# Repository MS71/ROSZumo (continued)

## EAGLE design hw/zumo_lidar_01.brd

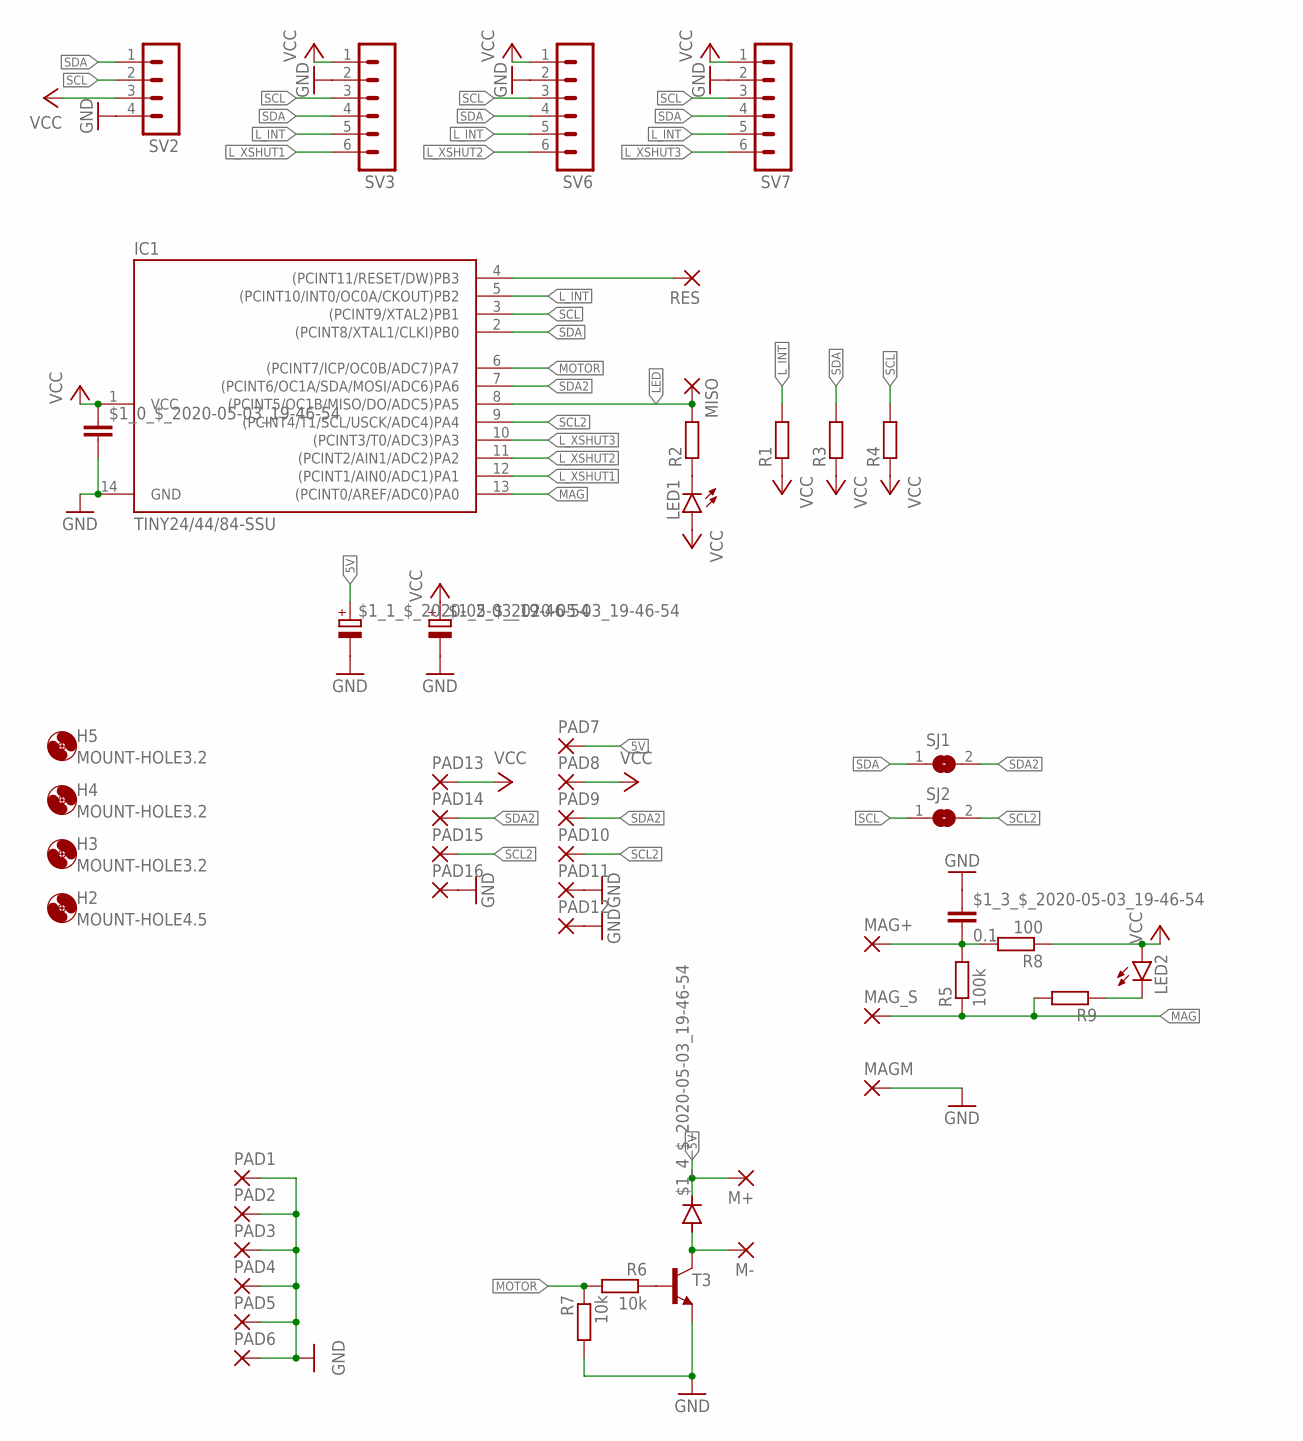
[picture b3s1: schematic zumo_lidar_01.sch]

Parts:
$1_0_$_2020-05-03_19-46-54: C-EUC0805; C0805
$1_1_$_2020-05-03_19-46-54, $1_2_$_2020-05-03_19-46-54: CPOL-EUSMCC; SMC_C
$1_3_$_2020-05-03_19-46-54: 0.1; C0805
$1_4_$_2020-05-03_19-46-54: DIODE-MINIMELF; MINIMELF
H2: MOUNT-HOLE4.5; 4,5
H3, H4, H5: MOUNT-HOLE3.2; 3,2
IC1: TINY24/44/84-SSU; SOIC14
LED1, LED2: LEDSML0805; SML0805
M+: 1,6/0,8
M-: 1,6/0,8
MAG+: 1,6/0,8
MAGM: 1,6/0,8
MAG_S: 1,6/0,8
MISO: 1,6/0,8
PAD1, PAD2, PAD3, PAD4, PAD5, PAD6: 2,54/1,1
PAD7, PAD8, PAD9, PAD10, PAD11, PAD12, PAD13, PAD14, PAD15, PAD16: 1,6/0,8
R1, R2, R3, R4, R9: R-EU_M0805; M0805
R5: 100k; M0805
R6, R7: 10k; R0805
R8: 100; M0805
RES: 1,6/0,8
SJ1, SJ2: SJ
SV2: MA04-1
SV3, SV6, SV7: MA06-1
T3: BC817-16-NPN-SOT23-BEC; SOT23-BEC

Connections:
5V: $1_1_$_2020-05-03_19-46-54.+, $1_4_$_2020-05-03_19-46-54.C, M+.1, PAD7.1
GND: $1_0_$_2020-05-03_19-46-54.2, $1_1_$_2020-05-03_19-46-54.-, $1_2_$_2020-05-03_19-46-54.-, $1_3_$_2020-05-03_19-46-54.1, IC1.14 (GND), MAGM.1, PAD1.1, PAD2.1, PAD3.1, PAD4.1, PAD5.1, PAD6.1, PAD11.1, PAD12.1, PAD16.1, R7.2, SV2.4, SV3.2, SV6.2, SV7.2, T3.E
LED: IC1.8 ((PCINT5/OC1B/MISO/DO/ADC5)PA5), MISO.1, R2.2
L_INT: IC1.5 ((PCINT10/INT0/OC0A/CKOUT)PB2), R1.2, SV3.5, SV6.5, SV7.5
L_XSHUT1: IC1.12 ((PCINT1/AIN0/ADC1)PA1), SV3.6
L_XSHUT2: IC1.11 ((PCINT2/AIN1/ADC2)PA2), SV6.6
L_XSHUT3: IC1.10 ((PCINT3/T0/ADC3)PA3), SV7.6
MAG: IC1.13 ((PCINT0/AREF/ADC0)PA0), MAG_S.1, R5.1, R9.2
MAGVCC: $1_3_$_2020-05-03_19-46-54.2, MAG+.1, R5.2, R8.2
MOTOR: IC1.6 ((PCINT7/ICP/OC0B/ADC7)PA7), R6.2, R7.1
unnamed: LED1.C, R2.1
unnamed: $1_4_$_2020-05-03_19-46-54.A, M-.1, T3.C
unnamed: R6.1, T3.B
unnamed: LED2.C, R9.1
RESET: IC1.4 ((PCINT11/RESET/DW)PB3), RES.1
SCL: IC1.3 ((PCINT9/XTAL2)PB1), R4.2, SJ2.1, SV2.2, SV3.3, SV6.3, SV7.3
SCL2: IC1.9 ((PCINT4/T1/SCL/USCK/ADC4)PA4), PAD10.1, PAD15.1, SJ2.2
SDA: IC1.2 ((PCINT8/XTAL1/CLKI)PB0), R3.2, SJ1.1, SV2.1, SV3.4, SV6.4, SV7.4
SDA2: IC1.7 ((PCINT6/OC1A/SDA/MOSI/ADC6)PA6), PAD9.1, PAD14.1, SJ1.2
VCC: $1_0_$_2020-05-03_19-46-54.1, $1_2_$_2020-05-03_19-46-54.+, IC1.1 (VCC), LED1.A, LED2.A, PAD8.1, PAD13.1, R1.1, R3.1, R4.1, R8.1, SV2.3, SV3.1, SV6.1, SV7.1

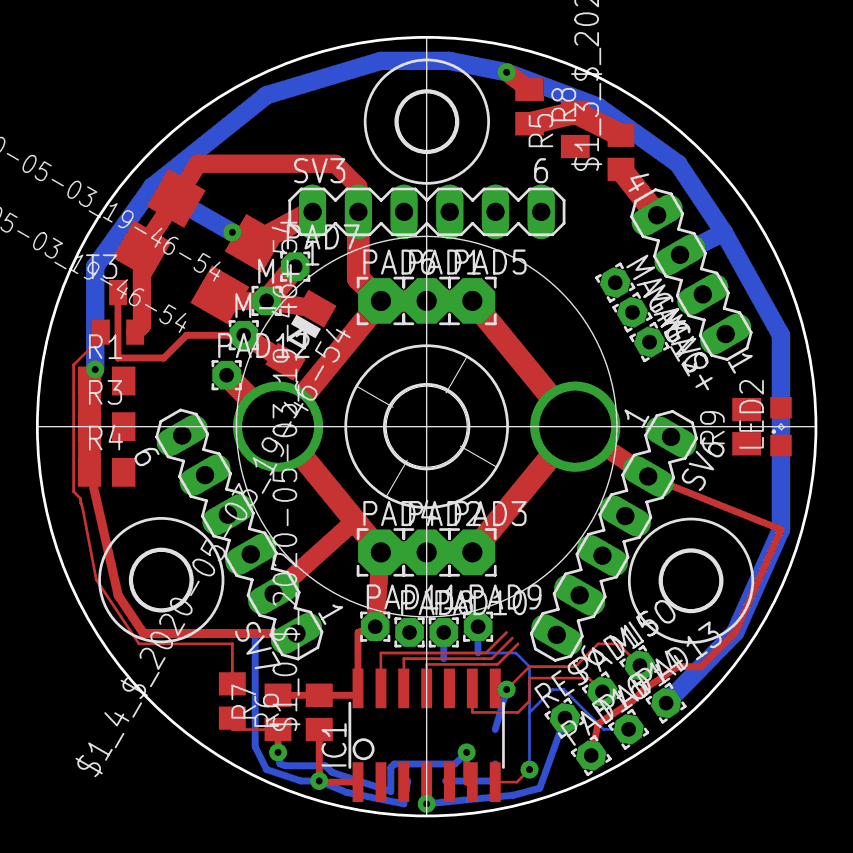
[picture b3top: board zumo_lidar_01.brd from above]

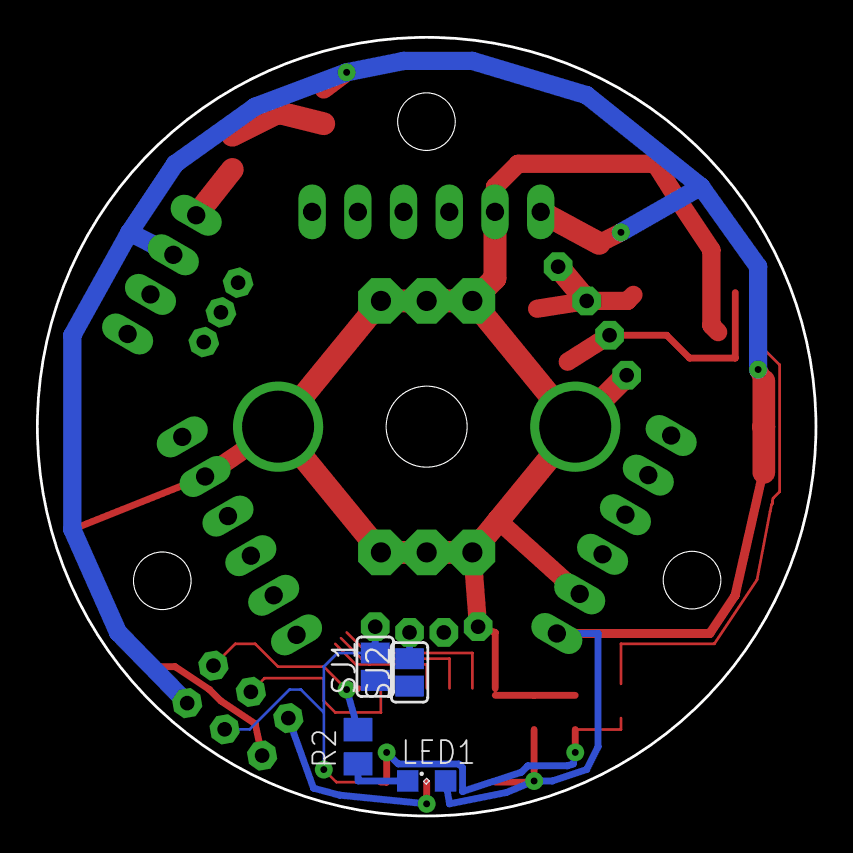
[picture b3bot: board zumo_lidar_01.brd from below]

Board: 2 copper layers, 43.3 x 43.3 mm, 51 parts (4 on the bottom side), 20 nets.

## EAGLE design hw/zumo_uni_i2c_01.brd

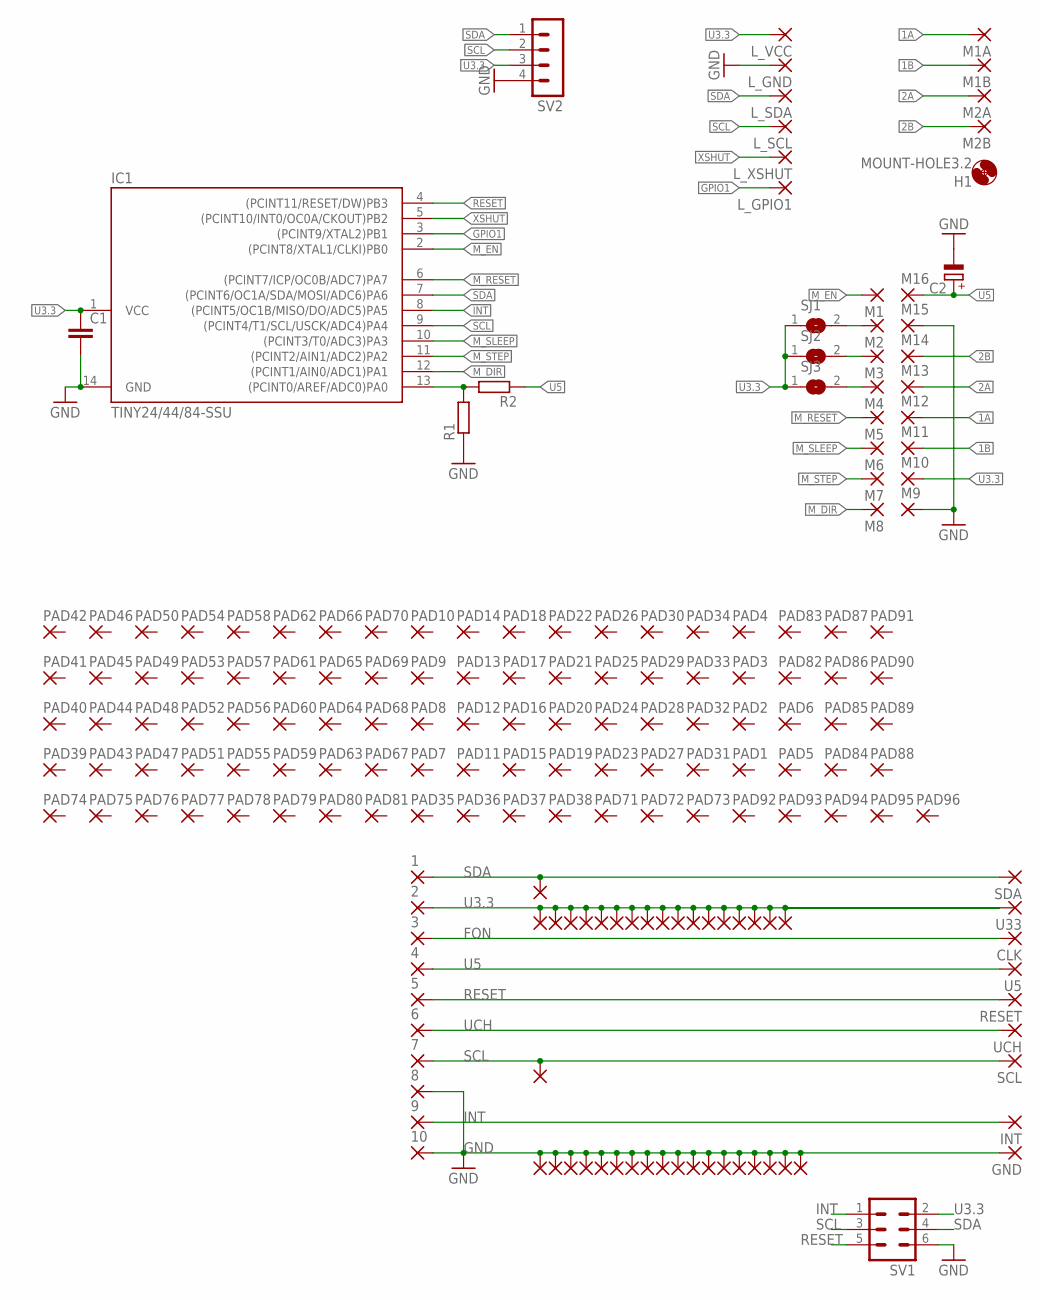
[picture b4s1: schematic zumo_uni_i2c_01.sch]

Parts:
1, 2, 3, 4, 5, 6, 7, 8, 9, 10: SMD2; SMD1,27-2,54
C1: C-EUC0805; C0805
C2: CPOL-EUSMCC; SMC_C
CLK: 1,6/0,9
GND: 1,6/0,9
H1: MOUNT-HOLE3.2; 3,2
IC1: TINY24/44/84-SSU; SOIC14
INT: 1,6/0,9
L_GND: 1,6/0,8
L_GPIO1: 1,6/0,8
L_SCL: 1,6/0,8
L_SDA: 1,6/0,8
L_VCC: 1,6/0,8
L_XSHUT: 1,6/0,8
M1, M2, M3, M4, M5, M6, M7, M8, M9, M10, M11, M12, M13, M14, M15, M16: 1,6/0,9
M1A, M1B, M2A, M2B: 1,6/0,8
MISO1, MISO4, MISO5, MISO6, MISO7, MISO8, MISO9, MISO10, MISO11, MISO12, MISO13, MISO14, MISO15, MISO16, MISO17, MISO18, MISO19, MISO20, MISO21, MISO22, MISO23, MISO24, MISO25, MISO26, MISO27, MISO28, MISO29, MISO30, MISO31, MISO32, MISO33, MISO34, MISO35, MISO36, MISO37, MISO41, MISO43: 1,6/0,9
PAD1, PAD2, PAD3, PAD4, PAD5, PAD6, PAD7, PAD8, PAD9, PAD10, PAD11, PAD12, PAD13, PAD14, PAD15, PAD16, PAD17, PAD18, PAD19, PAD20, PAD21, PAD22, PAD23, PAD24, PAD25, PAD26, PAD27, PAD28, PAD29, PAD30, PAD31, PAD32, PAD33, PAD34, PAD35, PAD36, PAD37, PAD38, PAD39, PAD40, PAD41, PAD42, PAD43, PAD44, PAD45, PAD46, PAD47, PAD48, PAD49, PAD50, PAD51, PAD52, PAD53, PAD54, PAD55, PAD56, PAD57, PAD58, PAD59, PAD60, PAD61, PAD62, PAD63, PAD64, PAD65, PAD66, PAD67, PAD68, PAD69, PAD70, PAD71, PAD72, PAD73, PAD74, PAD75, PAD76, PAD77, PAD78, PAD79, PAD80, PAD81, PAD82, PAD83, PAD84, PAD85, PAD86, PAD87, PAD88, PAD89, PAD90, PAD91, PAD92, PAD93, PAD94, PAD95, PAD96: 1,6/0,9
R1, R2: R-EU_M0805; M0805
RESET: 1,6/0,9
SCL: 1,6/0,9
SDA: 1,6/0,9
SJ1, SJ2, SJ3: SJ
SV1: ML6
SV2: MA04-1
U5, U33: 1,6/0,9
UCH: 1,6/0,9

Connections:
1A: M1A.1, M12.1
1B: M1B.1, M11.1
2A: M2A.1, M13.1
2B: M2B.1, M14.1
FON: 3.1, CLK.1
GND: 8.1, 10.1, C1.2, C2.-, GND.1, IC1.14 (GND), L_GND.1, M9.1, M15.1, MISO1.1, MISO5.1, MISO6.1, MISO7.1, MISO8.1, MISO9.1, MISO10.1, MISO11.1, MISO12.1, MISO13.1, MISO14.1, MISO15.1, MISO16.1, MISO17.1, MISO18.1, MISO19.1, MISO20.1, MISO43.1, R1.1, SV1.6, SV2.4
GPIO1: IC1.3 ((PCINT9/XTAL2)PB1), L_GPIO1.1
INT: 9.1, IC1.8 ((PCINT5/OC1B/MISO/DO/ADC5)PA5), INT.1, SV1.1
M_DIR: IC1.12 ((PCINT1/AIN0/ADC1)PA1), M8.1
M_EN: IC1.2 ((PCINT8/XTAL1/CLKI)PB0), M1.1
M_MS1: M2.1, SJ1.2
M_MS2: M3.1, SJ2.2
M_MS3: M4.1, SJ3.2
M_RESET: IC1.6 ((PCINT7/ICP/OC0B/ADC7)PA7), M5.1
M_SLEEP: IC1.10 ((PCINT3/T0/ADC3)PA3), M6.1
M_STEP: IC1.11 ((PCINT2/AIN1/ADC2)PA2), M7.1
unnamed: IC1.13 ((PCINT0/AREF/ADC0)PA0), R1.2, R2.2
RESET: 5.1, IC1.4 ((PCINT11/RESET/DW)PB3), RESET.1, SV1.5
SCL: 7.1, IC1.9 ((PCINT4/T1/SCL/USCK/ADC4)PA4), L_SCL.1, MISO41.1, SCL.1, SV1.3, SV2.2
SDA: 1.1, IC1.7 ((PCINT6/OC1A/SDA/MOSI/ADC6)PA6), L_SDA.1, MISO21.1, SDA.1, SV1.4, SV2.1
U3.3: 2.1, C1.1, IC1.1 (VCC), L_VCC.1, M10.1, MISO4.1, MISO22.1, MISO23.1, MISO24.1, MISO25.1, MISO26.1, MISO27.1, MISO28.1, MISO29.1, MISO30.1, MISO31.1, MISO32.1, MISO33.1, MISO34.1, MISO35.1, MISO36.1, MISO37.1, SJ1.1, SJ2.1, SJ3.1, SV1.2, SV2.3, U33.1
U5: 4.1, C2.+, M16.1, R2.1, U5.1
UCH: 6.1, UCH.1
XSHUT: IC1.5 ((PCINT10/INT0/OC0A/CKOUT)PB2), L_XSHUT.1

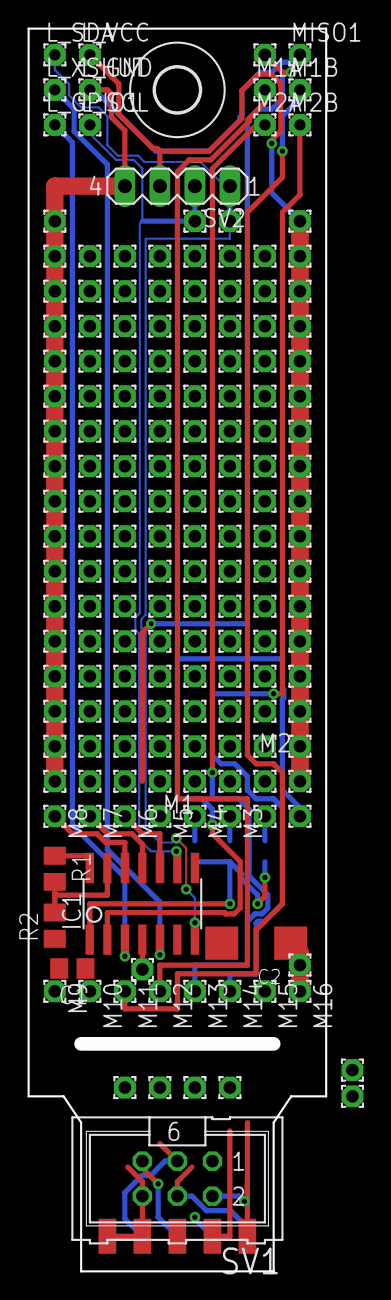
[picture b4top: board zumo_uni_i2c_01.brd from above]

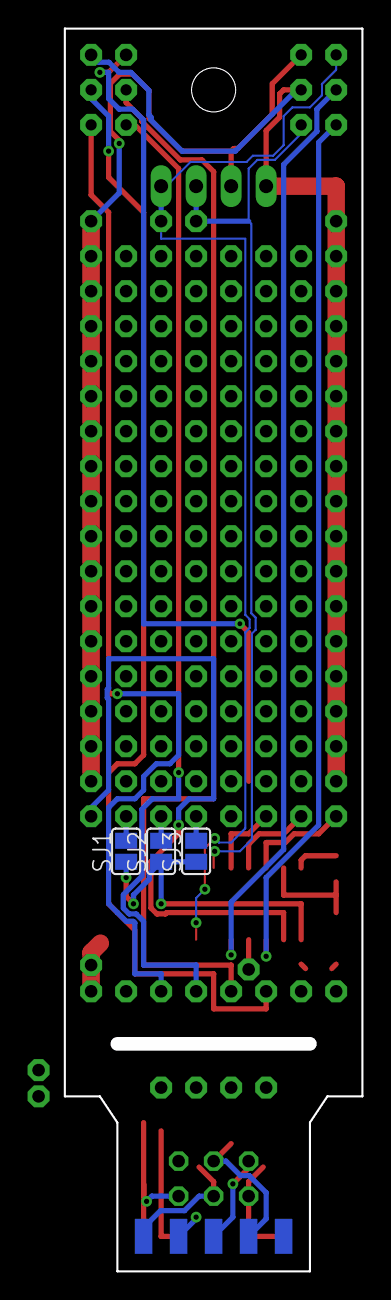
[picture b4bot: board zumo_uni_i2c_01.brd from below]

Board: 2 copper layers, 21.6 x 90.2 mm, 189 parts (8 on the bottom side), 24 nets.

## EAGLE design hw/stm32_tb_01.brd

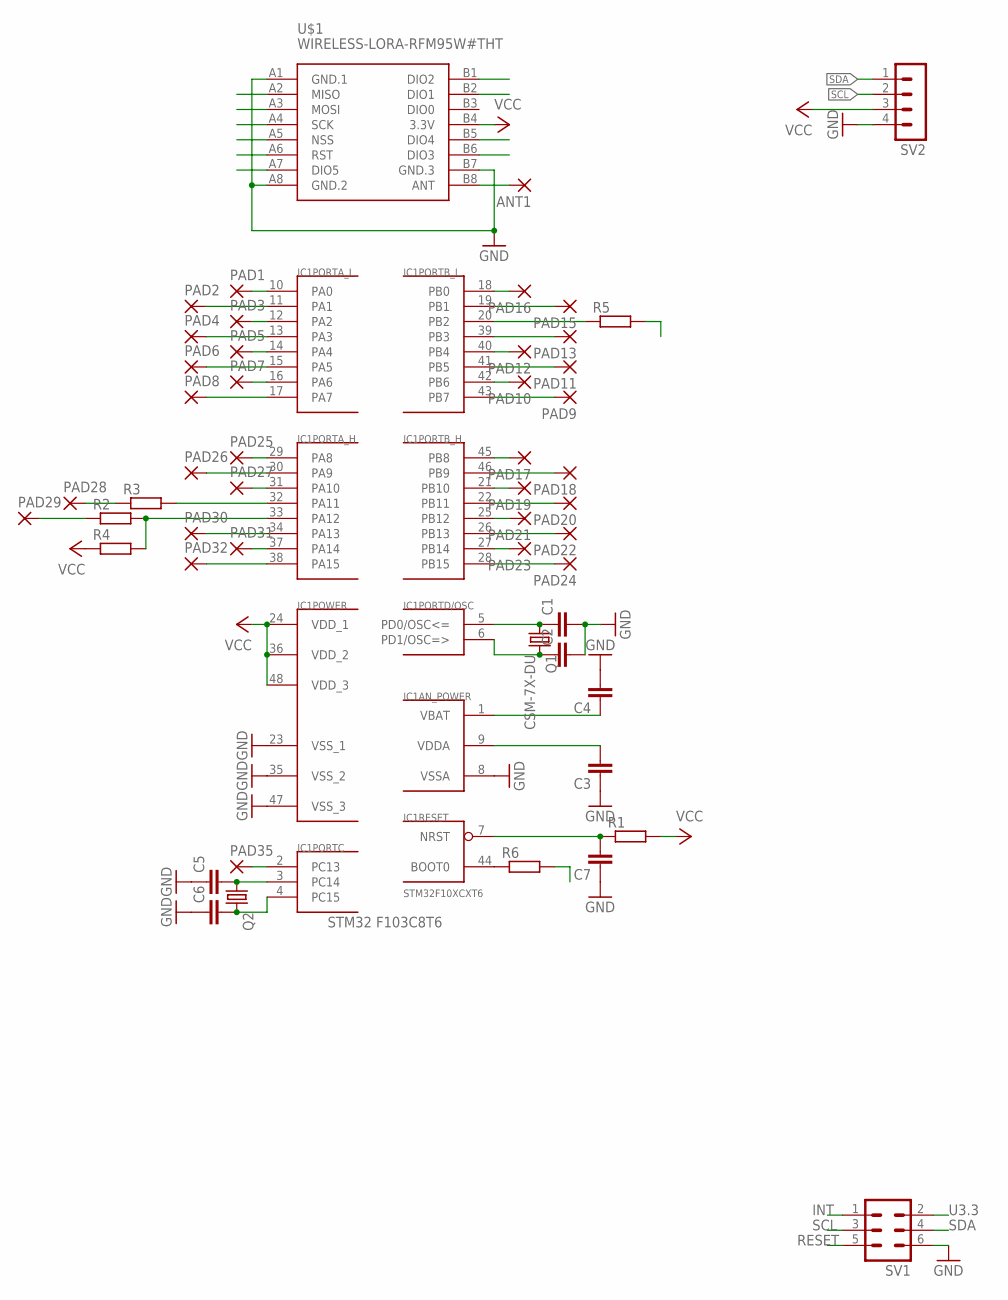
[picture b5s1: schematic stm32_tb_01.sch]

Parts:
ANT1: 1,6/0,9
C1, C2, C3, C4, C5, C6, C7: C-EUC0805; C0805
IC1: STM32F10XCXT6; TQFP48
PAD1, PAD2, PAD3, PAD4, PAD5, PAD6, PAD7, PAD8, PAD9, PAD10, PAD11, PAD12, PAD13, PAD15, PAD16, PAD17, PAD18, PAD19, PAD20, PAD21, PAD22, PAD23, PAD24, PAD25, PAD26, PAD27, PAD28, PAD29, PAD30, PAD31, PAD32, PAD35: 1,6/0,9
Q1: CSM-7X-DU
Q2: CRYSTALTC26V; TC26V
R1, R2, R3, R4, R5, R6: R-EU_R0805; R0805
SV1: ML6
SV2: MA04-1
U$1: WIRELESS-LORA-RFM95W#THT

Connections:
GND: C1.2, C2.2, C3.1, C4.2, C5.1, C6.1, C7.1, IC1.8 (VSSA), IC1.23 (VSS_1), IC1.35 (VSS_2), IC1.47 (VSS_3), SV1.6, SV2.4, U$1.A1 (GND.1), U$1.A8 (GND.2), U$1.B7 (GND.3)
INT: SV1.1
unnamed: IC1.10 (PA0), PAD1.1
unnamed: IC1.11 (PA1), PAD2.1
unnamed: IC1.12 (PA2), PAD3.1
unnamed: IC1.13 (PA3), PAD4.1
unnamed: IC1.14 (PA4), PAD5.1
unnamed: IC1.15 (PA5), PAD6.1
unnamed: IC1.16 (PA6), PAD7.1
unnamed: IC1.17 (PA7), PAD8.1
unnamed: IC1.43 (PB7), PAD9.1
unnamed: IC1.42 (PB6), PAD10.1
unnamed: IC1.41 (PB5), PAD11.1
unnamed: IC1.40 (PB4), PAD12.1
unnamed: IC1.39 (PB3), PAD13.1
unnamed: IC1.20 (PB2), R5.1
unnamed: IC1.19 (PB1), PAD15.1
unnamed: IC1.18 (PB0), PAD16.1
unnamed: IC1.45 (PB8), PAD17.1
unnamed: IC1.46 (PB9), PAD18.1
unnamed: IC1.21 (PB10), PAD19.1
unnamed: IC1.22 (PB11), PAD20.1
unnamed: IC1.25 (PB12), PAD21.1
unnamed: IC1.26 (PB13), PAD22.1
unnamed: IC1.27 (PB14), PAD23.1
unnamed: IC1.28 (PB15), PAD24.1
unnamed: IC1.29 (PA8), PAD25.1
unnamed: IC1.30 (PA9), PAD26.1
unnamed: IC1.31 (PA10), PAD27.1
unnamed: IC1.33 (PA12), R2.2, R4.2
unnamed: IC1.32 (PA11), R3.2
unnamed: IC1.34 (PA13), PAD30.1
unnamed: IC1.37 (PA14), PAD31.1
unnamed: IC1.38 (PA15), PAD32.1
unnamed: PAD28.1, R3.1
unnamed: PAD29.1, R2.1
unnamed: IC1.2 (PC13), PAD35.1
unnamed: C5.2, IC1.3 (PC14), Q2.1
unnamed: C6.2, IC1.4 (PC15), Q2.2
unnamed: IC1.44 (BOOT0), R6.1
unnamed: C1.1, IC1.5 (PD0/OSC<=), Q1.1
unnamed: C2.1, IC1.6 (PD1/OSC=>), Q1.2
unnamed: C3.2, IC1.9 (VDDA)
unnamed: C4.1, IC1.1 (VBAT)
unnamed: C7.2, IC1.7 (NRST), R1.1
unnamed: ANT1.1, U$1.B8 (ANT)
RESET: SV1.5
SCL: SV1.3, SV2.2
SDA: SV1.4, SV2.1
U3.3: SV1.2
VCC: IC1.24 (VDD_1), IC1.36 (VDD_2), IC1.48 (VDD_3), R1.2, R4.1, SV2.3, U$1.B4 (3.3V)

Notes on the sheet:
STM32 F103C8T6

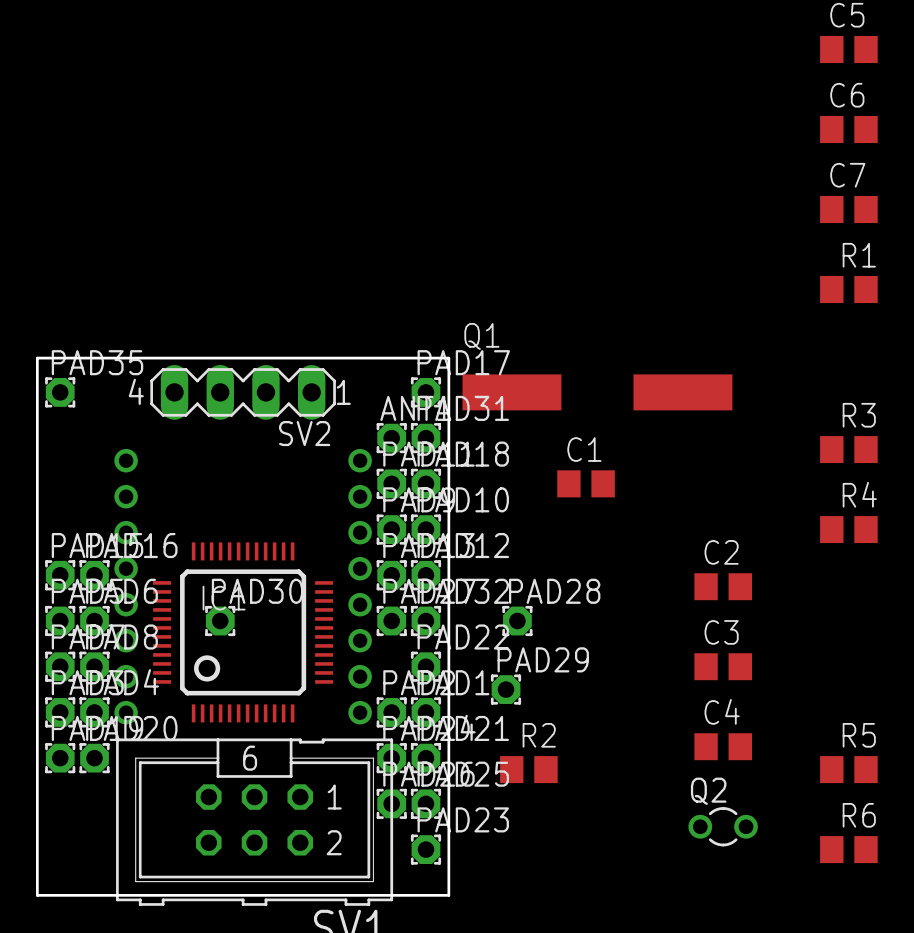
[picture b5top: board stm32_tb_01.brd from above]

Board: 2 copper layers, 22.9 x 29.8 mm, 52 parts (1 on the bottom side), 48 nets.

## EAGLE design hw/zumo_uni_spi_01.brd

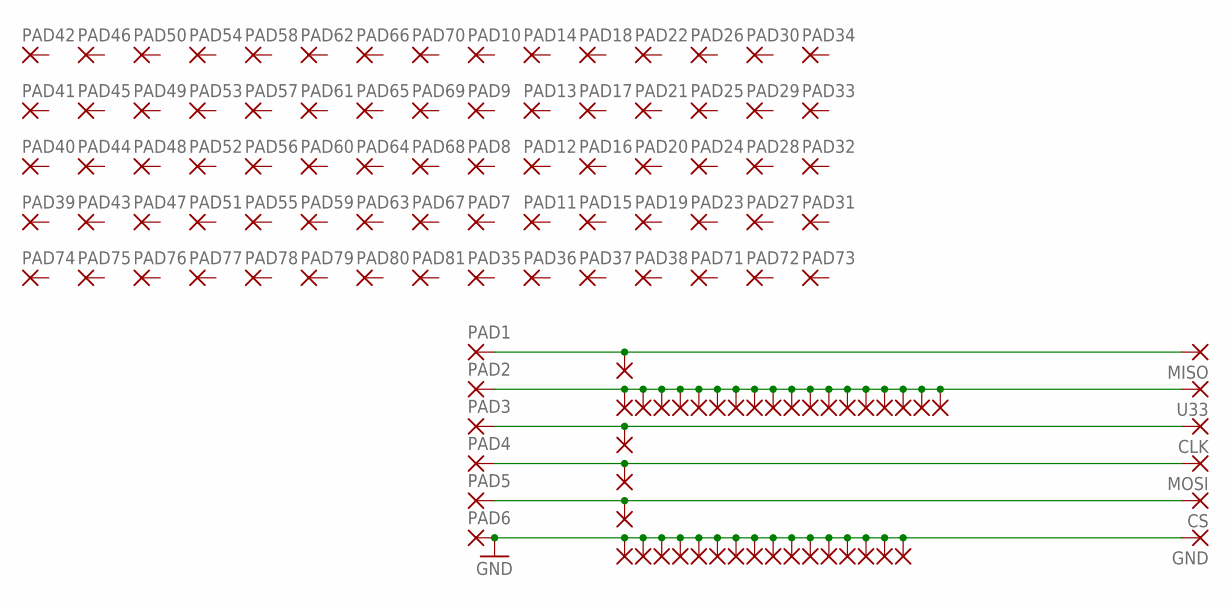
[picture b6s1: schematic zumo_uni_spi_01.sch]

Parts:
CLK: 1,6/0,9
CS: 1,6/0,9
GND: 1,6/0,9
MISO, MISO1, MISO2, MISO3, MISO4, MISO5, MISO6, MISO7, MISO8, MISO9, MISO10, MISO11, MISO12, MISO13, MISO14, MISO15, MISO16, MISO17, MISO18, MISO19, MISO20, MISO21, MISO22, MISO23, MISO24, MISO25, MISO26, MISO27, MISO28, MISO29, MISO30, MISO31, MISO32, MISO33, MISO34, MISO35, MISO36, MISO37, MISO38: 1,6/0,9
MOSI: 1,6/0,9
PAD1, PAD2, PAD3, PAD4, PAD5, PAD6: SMD2; SMD1,27-2,54
PAD7, PAD8, PAD9, PAD10, PAD11, PAD12, PAD13, PAD14, PAD15, PAD16, PAD17, PAD18, PAD19, PAD20, PAD21, PAD22, PAD23, PAD24, PAD25, PAD26, PAD27, PAD28, PAD29, PAD30, PAD31, PAD32, PAD33, PAD34, PAD35, PAD36, PAD37, PAD38, PAD39, PAD40, PAD41, PAD42, PAD43, PAD44, PAD45, PAD46, PAD47, PAD48, PAD49, PAD50, PAD51, PAD52, PAD53, PAD54, PAD55, PAD56, PAD57, PAD58, PAD59, PAD60, PAD61, PAD62, PAD63, PAD64, PAD65, PAD66, PAD67, PAD68, PAD69, PAD70, PAD71, PAD72, PAD73, PAD74, PAD75, PAD76, PAD77, PAD78, PAD79, PAD80, PAD81: 1,6/0,9
U33: 1,6/0,9

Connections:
GND: GND.1, MISO5.1, MISO6.1, MISO7.1, MISO8.1, MISO9.1, MISO10.1, MISO11.1, MISO12.1, MISO13.1, MISO14.1, MISO15.1, MISO16.1, MISO17.1, MISO18.1, MISO19.1, MISO20.1, PAD6.1
SPI_CLK: CLK.1, MISO3.1, PAD3.1
SPI_CS: CS.1, MISO1.1, PAD5.1
SPI_MISO: MISO.1, MISO21.1, PAD1.1
SPI_MOSI: MISO2.1, MOSI.1, PAD4.1
U3.3: MISO4.1, MISO22.1, MISO23.1, MISO24.1, MISO25.1, MISO26.1, MISO27.1, MISO28.1, MISO29.1, MISO30.1, MISO31.1, MISO32.1, MISO33.1, MISO34.1, MISO35.1, MISO36.1, MISO37.1, MISO38.1, PAD2.1, U33.1

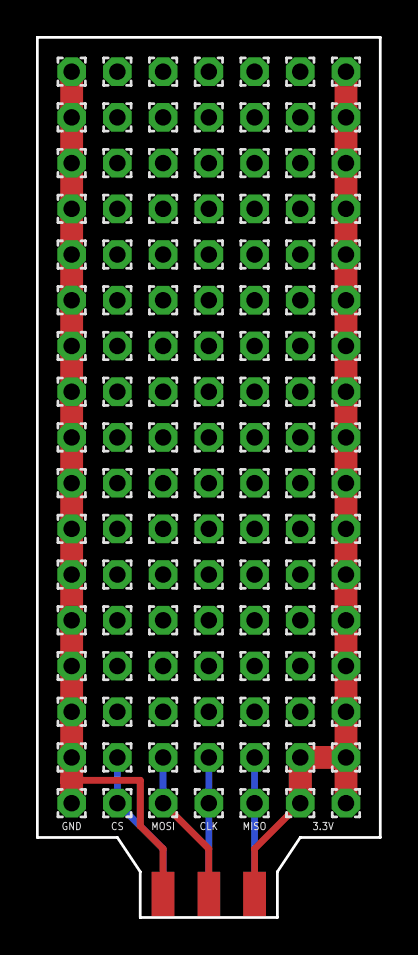
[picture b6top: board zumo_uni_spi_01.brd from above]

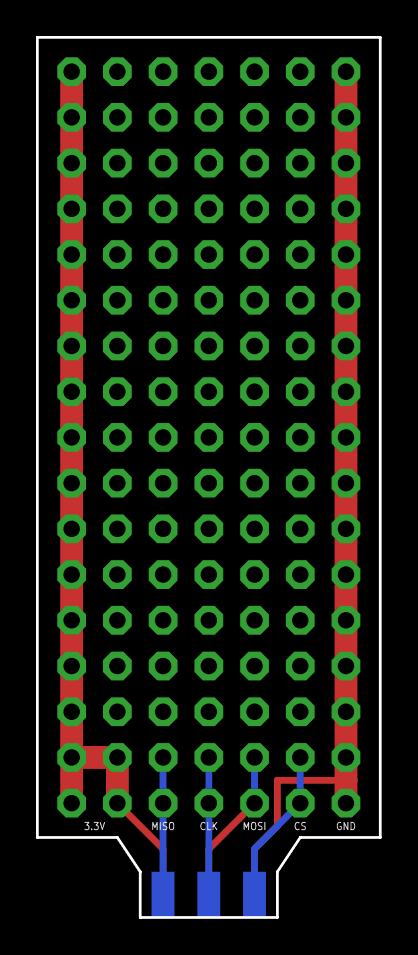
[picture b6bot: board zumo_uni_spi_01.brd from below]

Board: 2 copper layers, 19.0 x 48.9 mm, 125 parts (3 on the bottom side), 6 nets.

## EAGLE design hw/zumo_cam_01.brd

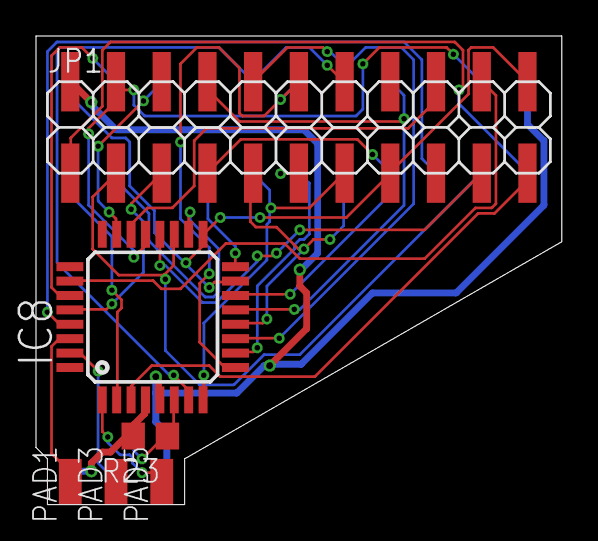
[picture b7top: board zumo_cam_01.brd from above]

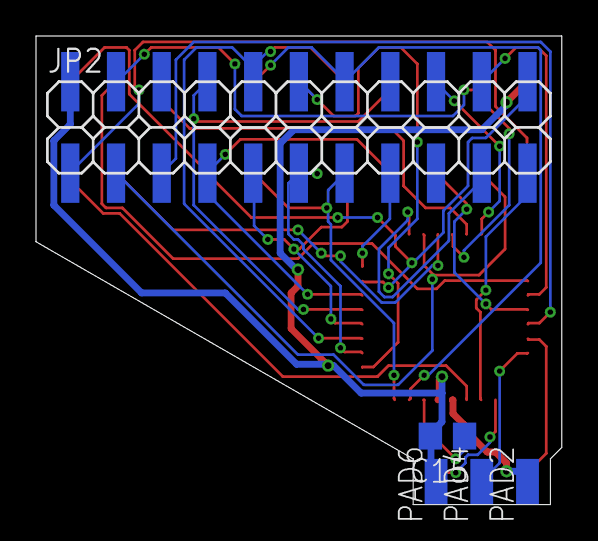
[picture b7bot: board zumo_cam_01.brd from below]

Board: 2 copper layers, 29.2 x 26.0 mm, 11 parts (5 on the bottom side), 29 nets.

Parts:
C15: 0.1; C0805
IC8: STM32G071KBT6N; LQFP-32
JP1, JP2: 2X11SMD
PAD1, PAD2, PAD3, PAD4, PAD5, PAD6: SMD1,27-2,54
R23: 100K; R0805

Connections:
+3V3: JP1.1, JP2.1
CL_OE: IC8.26, JP1.20
CL_RCK: IC8.22, JP1.18
CL_RST: IC8.15, IC8.17, JP1.15, JP1.22, JP2.22
CL_VSYNC: IC8.28, JP1.5
CL_WR: IC8.20, JP1.19
CL_WRST: IC8.3, JP1.21
CR_OE: IC8.27, JP2.20
CR_RCK: IC8.23, JP2.18
CR_RST: IC8.16, JP2.15
CR_VSYNC: IC8.29, JP2.5
CR_WR: IC8.18, JP2.19
CR_WRST: IC8.2, JP2.21
C_D0: IC8.7, JP1.14, JP2.14
C_D1: IC8.8, JP1.13, JP2.13
C_D2: IC8.9, JP1.12, JP2.12
C_D3: IC8.10, JP1.11, JP2.11
C_D4: IC8.11, JP1.10, JP2.10
C_D5: IC8.12, JP1.9, JP2.9
C_D6: IC8.13, JP1.8, JP2.8
C_D7: IC8.14, JP1.7, JP2.7
GND: C15.2, IC8.5, JP1.2, JP2.2, PAD6.1
SCL: IC8.19, JP1.3, JP2.3
SDA: IC8.21, JP1.4, JP2.4
SPI_CS: IC8.1, PAD5.1
SPI_MISO: IC8.30, PAD1.1
SPI_MOSI: IC8.31, PAD4.1
SWNRES: C15.1, IC8.6, R23.1
U3.3: IC8.4, PAD2.1, R23.2

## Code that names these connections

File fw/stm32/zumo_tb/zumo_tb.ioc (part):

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PB13.GPIOParameters=GPIO_Label
PC7.GPIOParameters=GPIO_Label
PC15-OSC32_OUT\ (PC15).GPIO_Speed=GPIO_SPEED_FREQ_LOW
PA12\ [PA10].GPIO_Label=SPI_MOSI
PC12.Signal=GPIO_Input
PB14.GPIO_Label=I_BUS_FON
PD3.GPIOParameters=GPIO_Label
PC6.GPIO_Label=O_L_RST_9
PA6.GPIO_Label=RPI_CS0
PB6.GPIO_Label=O_L_RST_6
PD2.GPIOParameters=GPIO_Label
PB13.Signal=GPIO_Output
PD6.GPIO_Label=O_FLASH_WP
PA2.GPIOParameters=PinState,GPIO_Label
RCC.SYSCLKSource=RCC_SYSCLKSOURCE_PLLCLK
PA12\ [PA10].Signal=SPI1_MOSI
PD4.Signal=GPIO_Output
PB6.Signal=GPIO_Output
PC7.Signal=GPIO_Output
PC3.Signal=SPI2_MOSI
PD0.Signal=S_TIM16_CH1
PD8.Signal=GPIO_Output
PB2.Signal=USART3_TX
PD1.GPIOParameters=GPIO_Label
PD1.GPIO_Label=O_BUS_RESET
PB12.GPIO_Label=O_L_RST_10
PA12\ [PA10].GPIOParameters=GPIO_Speed,GPIO_Label
PB0.GPIOParameters=GPIO_Label
PA1.GPIOParameters=GPIO_Label
PC4.GPIO_Label=U1_ESP_RXD
PA5.GPIO_PuPd=GPIO_NOPULL
PB1.GPIO_Label=O_L_RST_1
PA0.Mode=IN0
PA8.Signal=GPIO_Output
PA8.GPIO_ModeDefaultOutputPP=GPIO_MODE_OUTPUT_PP
PA0.Signal=ADC1_IN0
PC8.GPIOParameters=GPIO_Label
Mcu.Package=LQFP64
PB9.Signal=SPI2_NSS
PB1.Signal=GPIO_Output
PD5.GPIOParameters=GPIO_Label
PA10.Signal=I2C1_SDA
PA5.GPIOParameters=GPIO_Speed,GPIO_PuPd,GPIO_Label
PB14.GPIOParameters=GPIO_Label
PB10.GPIOParameters=GPIO_Label
PA4.GPIO_Label=O_L_RST_10
PC4.GPIOParameters=GPIO_Label
PA5.Mode=Full_Duplex_Master
PA6.GPIOParameters=GPIO_Label
PD6.GPIOParameters=GPIO_Label
PC15-OSC32_OUT\ (PC15).GPIO_Label=O_INT
PD9.GPIO_Label=O_FLASH_CS
PA12\ [PA10].GPIO_Speed=GPIO_SPEED_FREQ_VERY_HIGH
PA15.GPIOParameters=GPIO_Speed,GPIO_Label
PC13.Signal=GPIO_Input
PD3.Signal=GPIO_Output
PC6.Signal=GPIO_Output
PC2.Signal=SPI2_MISO
PD1.Signal=GPIO_Output
PC0.Signal=GPIO_Output
PC11.GPIOParameters=GPIO_Label
PA9.GPIO_FMPA9=__NULL
PC14-OSC32_IN\ (PC14).GPIO_Label=RPI_18
PA3.Mode=Asynchronous
PA8.GPIO_Label=O_CHARGE_ON
PB11.Mode=Asynchronous
PC15-OSC32_OUT\ (PC15).GPIO_ModeDefaultOutputPP=GPIO_MODE_OUTPUT_OD
PA9.Signal=I2C1_SCL
PB10.Signal=I2C2_SCL
PB14.Signal=GPIO_Input
PA5.Signal=SPI1_SCK
PA1.Mode=IN1
PB4.GPIO_Label=O_L_RST_4
PB15.GPIO_Label=ZUMO_SHDN
PA1.GPIO_Label=ADC1
PC10.GPIOParameters=GPIO_Label
PA13.Mode=Serial_Wire
PC9.GPIOParameters=GPIO_Label
PC7.GPIO_Label=O_L_RST_8
PA4.Signal=GPIO_Output
PB5.Signal=GPIO_Output
PA5.GPIO_Label=SPI_CLK
PC12.GPIO_Label=RPI_15
PA0.GPIOParameters=GPIO_Label
PD0.GPIOParameters=GPIO_Label
PD2.Signal=GPIO_Output
PB0.Signal=USART3_RX
PA7.GPIOParameters=GPIO_Label
PC1.Signal=GPIO_Output
PB12.GPIOParameters=GPIO_Label
PD2.GPIO_Label=O_BNO055_RESET
PA11\ [PA9].Mode=Full_Duplex_Master
Mcu.UserName=STM32G081RBTx
PD9.GPIOParameters=GPIO_Label
PA11\ [PA9].GPIO_Label=SPI_MISO
PA12\ [PA10].Mode=Full_Duplex_Master
PC10.Signal=GPIO_Input
PA0.GPIO_Label=ADC0
PA14-BOOT0.Mode=Serial_Wire
PC0.GPIOParameters=GPIO_Label
PA9.GPIOParameters=GPIO_Speed,GPIO_FMPA9
PD0.GPIO_Label=O_LIDAR_M
PC0.GPIO_Label=O_CAM_PWDN
PB0.GPIO_Label=U3_ZUMO_TXD
PC13.GPIO_Label=RPI_16
PB13.GPIO_Label=O_L_RST_11
PB11.Signal=LPUART1_TX
PB15.Signal=GPIO_Input
PB5.GPIOParameters=GPIO_Label
PA15.GPIO_Label=SPI_CS
PB4.GPIOParameters=GPIO_Label
PC15-OSC32_OUT\ (PC15).GPIOParameters=GPIO_Speed,GPIO_PuPd,GPIO_Label,GPIO_ModeDefaultOutputPP
PC1.GPIOParameters=GPIO_Label
PD8.GPIOParameters=GPIO_Label
PA8.GPIOParameters=PinState,GPIO_PuPd,GPIO_Label,GPIO_ModeDefaultOutputPP
PA14-BOOT0.Signal=SYS_SWCLK
RCC.HSE_VALUE=4000000
PA11\ [PA9].GPIOParameters=GPIO_Speed,GPIO_Label
PA15.Mode=NSS_Signal_Hard_Output
PA2.PinState=GPIO_PIN_RESET
PC11.GPIO_Label=RPI_14
PB3.GPIOParameters=GPIO_Label
PB7.Signal=GPIO_Output
PB6.GPIOParameters=GPIO_Label
PB7.GPIO_Label=O_L_RST_7
PA6.Signal=GPIO_Input
PB15.GPIO_PuPd=GPIO_PULLUP
PD5.GPIO_Label=O_FLASH_HOLD
PA2.GPIO_Label=O_LED2
PA15.Signal=SPI1_NSS
PA10.GPIO_Speed=GPIO_SPEED_FREQ_LOW
PB5.GPIO_Label=O_L_RST_5
PC5.Signal=USART1_RX
PD3.GPIO_Label=O_L_RST_0
PD6.Signal=GPIO_Output
PA8.PinState=GPIO_PIN_RESET
PB4.Signal=GPIO_Output
PA3.Signal=LPUART1_RX
PB3.GPIO_Label=O_L_RST_3
PA11\ [PA9].GPIO_Speed=GPIO_SPEED_FREQ_VERY_HIGH
PC10.GPIO_Label=RPI_13
PA10.Mode=I2C
PC9.GPIO_Label=RPI_12
PC11.Signal=GPIO_Input
PC8.Signal=GPIO_Input
PC4.Signal=USART1_TX
PD5.Signal=GPIO_Output
PD9.Signal=GPIO_Output
PC15-OSC32_OUT\ (PC15).Signal=GPIO_Output
PD8.GPIO_Label=O_LEDSTRB
PC12.GPIOParameters=GPIO_Label
PC8.GPIO_Label=RPI_11
PA13.Signal=SYS_SWDIO
PA9.Mode=I2C
PB10.GPIO_Label=SCL2
PB7.GPIOParameters=GPIO_Label
PC5.GPIOParameters=GPIO_Label
PB2.GPIOParameters=GPIO_Label
PA1.Signal=ADC1_IN1
board=custom
PC15-OSC32_OUT\ (PC15).GPIO_PuPd=GPIO_PULLUP
PA10.GPIO_FMPA10=__NULL
PD4.GPIO_Label=O_L_RST_2
PC13.GPIOParameters=GPIO_Label
PC1.GPIO_Label=O_LED1
PA10.GPIOParameters=GPIO_FMPA10,GPIO_Speed
PD4.GPIOParameters=GPIO_Label
PA4.GPIOParameters=GPIO_Label
PB15.GPIOParameters=GPIO_PuPd,GPIO_Label
Mcu.Name=STM32G081RBTx
PA11\ [PA9].Signal=SPI1_MISO
PA2.Signal=GPIO_Output
PB3.Signal=GPIO_Output
RCC.SYSCLKFreq_VALUE=64000000
PA7.GPIO_Label=RPI_CS1
PC5.GPIO_Label=U1_ESP_TXD
PC14-OSC32_IN\ (PC14).Signal=GPIO_Input
PA15.GPIO_Speed=GPIO_SPEED_FREQ_VERY_HIGH
PB2.GPIO_Label=U3_ZUMO_RXD
PC6.GPIOParameters=GPIO_Label
PA8.GPIO_PuPd=GPIO_NOPULL
PC14-OSC32_IN\ (PC14).GPIOParameters=GPIO_Label
PA5.GPIO_Speed=GPIO_SPEED_FREQ_VERY_HIGH
PA9.GPIO_Speed=GPIO_SPEED_FREQ_LOW
PB8.Signal=SPI2_SCK
PC9.Signal=GPIO_Input
PB12.Signal=GPIO_Output
PB1.GPIOParameters=GPIO_Label
PA7.Signal=GPIO_Input

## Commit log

2020-01-24 added
2020-01-24 i2c api added
2020-01-28 pm added
2020-02-02 some files added
2020-02-09 terminal added
2020-04-04 some files added and some firmware changes
2020-04-20 i2c terminal added
2020-04-23 some optimiziations
2020-09-26 stm32 firmware improved
2020-09-27 some monification for new pcb
2020-10-01 some 3d parts added and wireless charging fixed
2020-11-13 image updated
2020-11-13 iimage updated
2020-12-13 urdf added
2020-12-13 stm32 code improved
2021-01-19 stm32 cube fw updated
2021-03-12 uart added
2021-03-13 lds pwm enabled
2021-03-13 LDS uart decoder implemented
2021-03-14 lds support in i2c driver implemented
